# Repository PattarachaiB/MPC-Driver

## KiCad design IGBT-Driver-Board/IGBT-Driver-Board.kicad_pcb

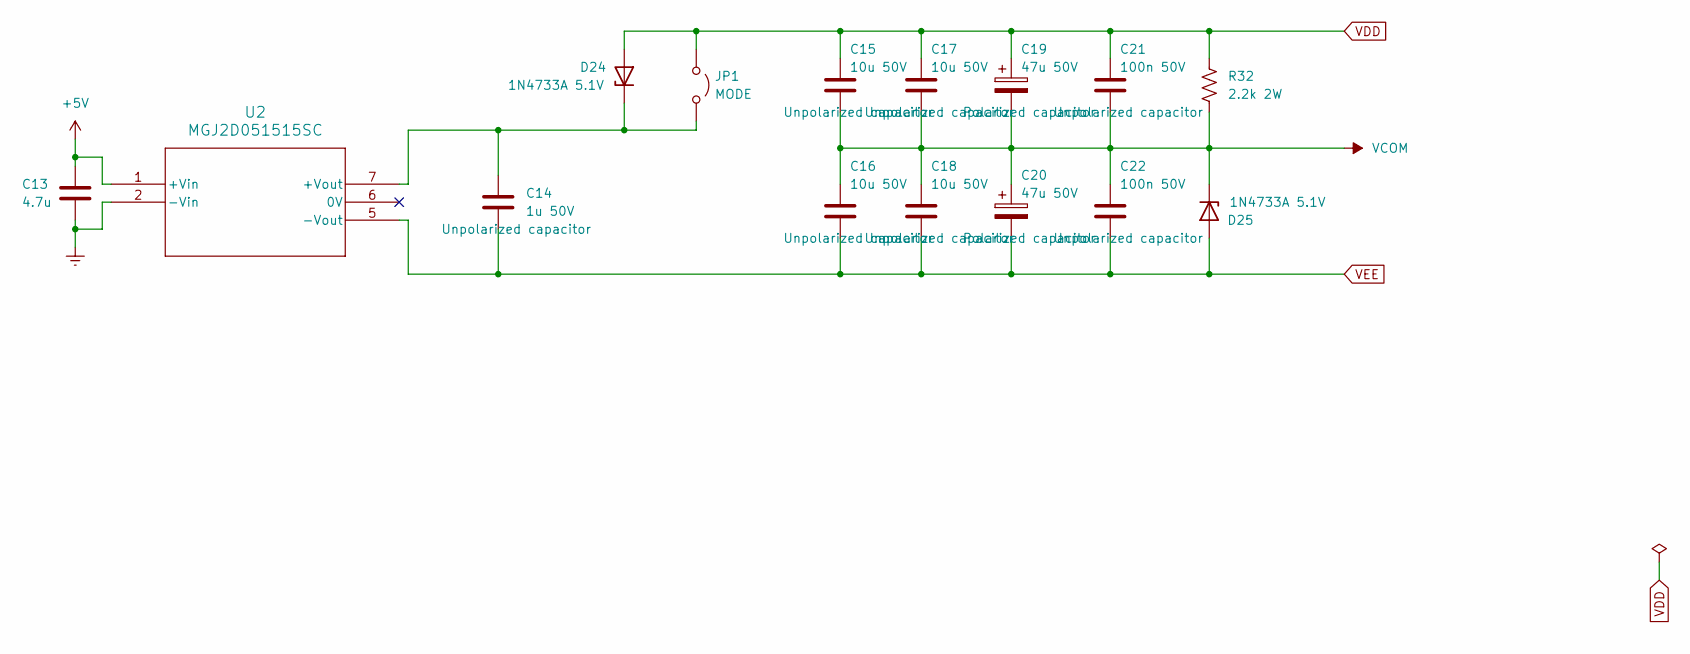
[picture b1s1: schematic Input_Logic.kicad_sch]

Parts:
C13: 4.7u; RDEC71H475K2M1H03A
C14: 1u 50V; K105M20X7RF5UH5_VIS
C15, C16, C17, C18: 10u 50V; RDEC71H106K3K1H03B
C19, C20: 47u 50V; CP_Radial_D6.3mm_P2.50mm
C21, C22: 100n 50V; RDER71H104K0M1H03A
D24, D25: 1N4733A 5.1V; D_DO-41_SOD81_P7.62mm_Horizontal
JP1: MODE; PinHeader_1x02_P2.54mm_Vertical
R32: 2.2k 2W; R_Axial_DIN0516_L15.5mm_D5.0mm_P20.32mm_Horizontal
U2: MGJ2D051515SC; MGJ2_MUR

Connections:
+5V: C13.1, U2.1 (+Vin); also elsewhere on the board
GNDREF: C13.2, U2.2 (-Vin); also elsewhere on the board
unnamed: C14.1, D24.1 (K), JP1.2 (B), U2.7 (+Vout)
VCOM: C15.2, C16.1, C17.2, C18.1, C19.2, C20.1, C21.2, C22.1, D25.1 (K), R32.1; also elsewhere on the board
VDD: C15.1, C17.1, C19.1, C21.1, D24.2 (A), JP1.1 (A), R32.2; also elsewhere on the board
VEE: C14.2, C16.2, C18.2, C20.2, C22.2, D25.2 (A), U2.5 (-Vout); also elsewhere on the board

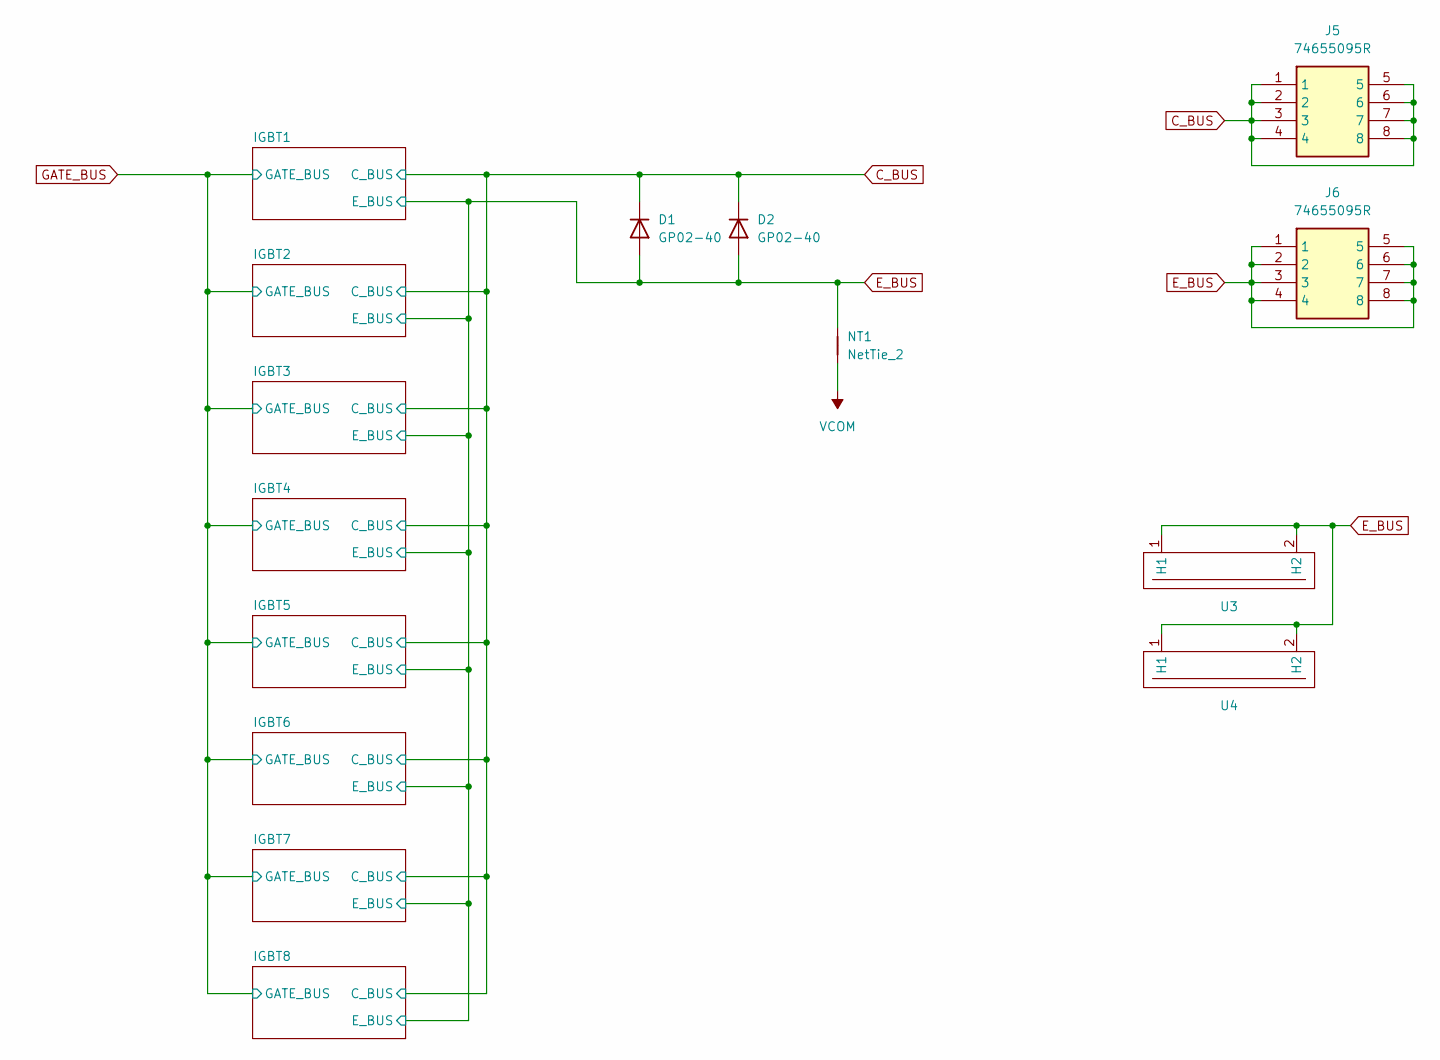
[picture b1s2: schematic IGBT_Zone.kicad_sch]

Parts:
D1, D2: GP02-40; D_DO-41_P20.32mm_HV_Horizontal
J5, J6: 74655095R; Mouser Part Number 710-74655095R
NT1: NetTie_2; NetTie-2_SMD_Pad6.0mm
U3: Heatsink_150x20x6mm
U4: Heatsink_150x20x6mm_flip

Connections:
C_BUS: D1.1 (K), D2.1 (K), J5.1, J5.2, J5.3, J5.4, J5.5, J5.6, J5.7, J5.8; also elsewhere on the board
E_BUS: D1.2 (A), D2.2 (A), J6.1, J6.2, J6.3, J6.4, J6.5, J6.6, J6.7, J6.8, NT1.2, U3.1 (H1), U3.2 (H2), U4.1 (H1), U4.2 (H2); also elsewhere on the board
VCOM: NT1.1; also elsewhere on the board

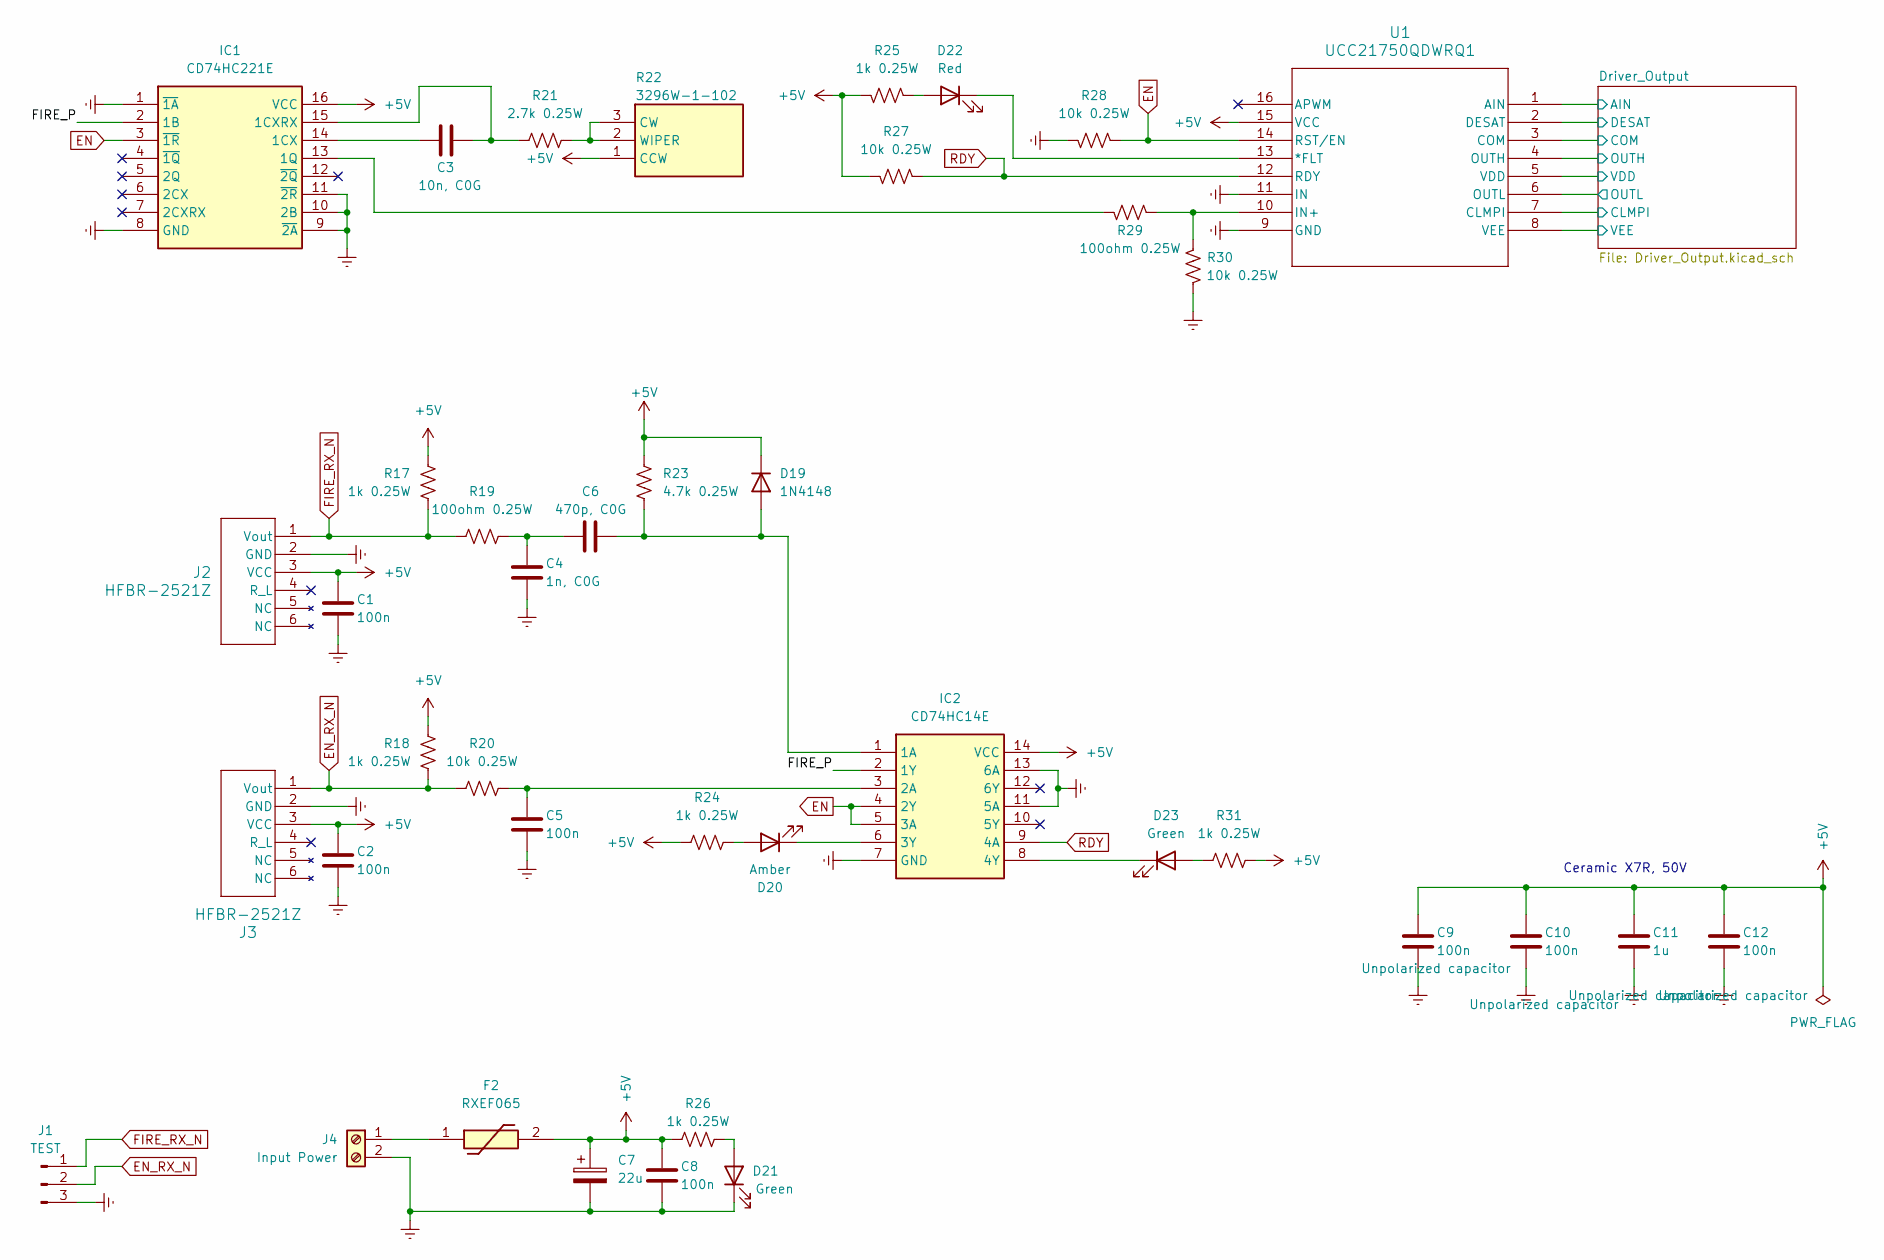
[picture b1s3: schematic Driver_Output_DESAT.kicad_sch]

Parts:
C1, C2, C5, C8, C9, C10, C12: 100n; RDER71H104K0M1H03A
C3: 10n, C0G; C330C103J5G5TA
C4: 1n, C0G; C330C103J5G5TA
C6: 470p, C0G; C330C103J5G5TA
C7: 22u; CP_Radial_D5.0mm_P2.00mm
C11: 1u; K105M20X7RF5UH5_VIS
D19: 1N4148; D_DO-35_SOD27_P7.62mm_Horizontal
D20: Amber; LED_D5.0mm_Clear
D21, D23: Green; LED_D5.0mm_Clear
D22: Red; LED_D5.0mm_Clear
F2: RXEF065; Mouser Part Number 650-RXEF065
IC1: CD74HC221E; DIP794W53P254L1930H508Q16N; Mouser Part Number 595-CD74HC221E
IC2: CD74HC14E; DIP794W53P254L1930H508Q14N; Mouser Part Number 595-CD74HC14E
J1: TEST; PinHeader_1x03_P2.54mm_Vertical
J2, J3: HFBR-2521Z
J4: Input Power; TerminalBlock_Phoenix_MKDS-1,5-2_1x02_P5.00mm_Horizontal
R17, R18, R24, R25, R26, R31: 1k 0.25W; R_Axial_DIN0207_L6.3mm_D2.5mm_P10.16mm_Horizontal
R19, R29: 100ohm 0.25W; R_Axial_DIN0207_L6.3mm_D2.5mm_P10.16mm_Horizontal
R20, R27, R28, R30: 10k 0.25W; R_Axial_DIN0207_L6.3mm_D2.5mm_P10.16mm_Horizontal
R21: 2.7k 0.25W; R_Axial_DIN0207_L6.3mm_D2.5mm_P10.16mm_Horizontal
R22: 3296W-1-102; 3296W1503LF; Mouser Part Number 652-3296W-1-104
R23: 4.7k 0.25W; R_Axial_DIN0207_L6.3mm_D2.5mm_P10.16mm_Horizontal
U1: UCC21750QDWRQ1; SOIC16_DW_TEX

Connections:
+5V: C1.1, C2.1, C7.1, C8.1, C9.1, C10.1, C11.1, C12.1, D19.1 (K), F2.2, IC1.16 (VCC), IC2.14 (VCC), J2.3 (VCC), J3.3 (VCC), R17.2, R18.2, R22.1 (CCW), R23.2, R24.1, R25.2, R26.2, R27.2, R31.2, U1.15 (VCC); also elsewhere on the board
/Driver_Output_DESAT/Driver_Output/DESAT: U1.2 (DESAT); also elsewhere on the board
/Driver_Output_DESAT/FIRE_P: IC1.2 (1B), IC2.2 (1Y)
EN: IC1.3 (~1R), IC2.4 (2Y), IC2.5 (3A), R28.1, U1.14 (RST/EN)
EN_RX_N: J1.2, J3.1 (Vout), R18.1, R20.1
FIRE_RX_N: J1.1, J2.1 (Vout), R17.1, R19.1
GATE_BUS: U1.4 (OUTH), U1.6 (OUTL), U1.7 (CLMPI); also elsewhere on the board
GNDREF: C1.2, C2.2, C4.2, C5.2, C7.2, C8.2, C9.2, C10.2, C11.2, C12.2, D21.1 (K), IC1.1 (~1A), IC1.8 (GND), IC1.9 (~2A), IC1.10 (2B), IC1.11 (~2R), IC2.7 (GND), IC2.11 (5A), IC2.13 (6A), J1.3, J2.2 (GND), J3.2 (GND), J4.2, R28.2, R30.2, U1.9 (GND), U1.11 (IN); also elsewhere on the board
unnamed: C4.1, C6.2, R19.2
unnamed: C6.1, D19.2 (A), IC2.1 (1A), R23.1
unnamed: D20.2 (A), R24.2
unnamed: D20.1 (K), IC2.6 (3Y)
unnamed: D21.2 (A), R26.1
unnamed: D22.2 (A), R25.1
unnamed: D22.1 (K), U1.13 (*FLT)
unnamed: D23.2 (A), R31.1
unnamed: D23.1 (K), IC2.8 (4Y)
unnamed: C3.1, IC1.14 (1CX)
unnamed: C3.2, IC1.15 (1CXRX), R21.2
unnamed: IC1.13 (1Q), R29.2
unnamed: C5.1, IC2.3 (2A), R20.2
unnamed: F2.1, J4.1
unnamed: R21.1, R22.2 (WIPER), R22.3 (CW)
unnamed: R29.1, R30.1, U1.10 (IN+)
RDY: IC2.9 (4A), R27.1, U1.12 (RDY)
VCOM: U1.1 (AIN), U1.3 (COM); also elsewhere on the board
VDD: U1.5 (VDD); also elsewhere on the board
VEE: U1.8 (VEE); also elsewhere on the board

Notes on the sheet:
Ceramic X7R, 50V

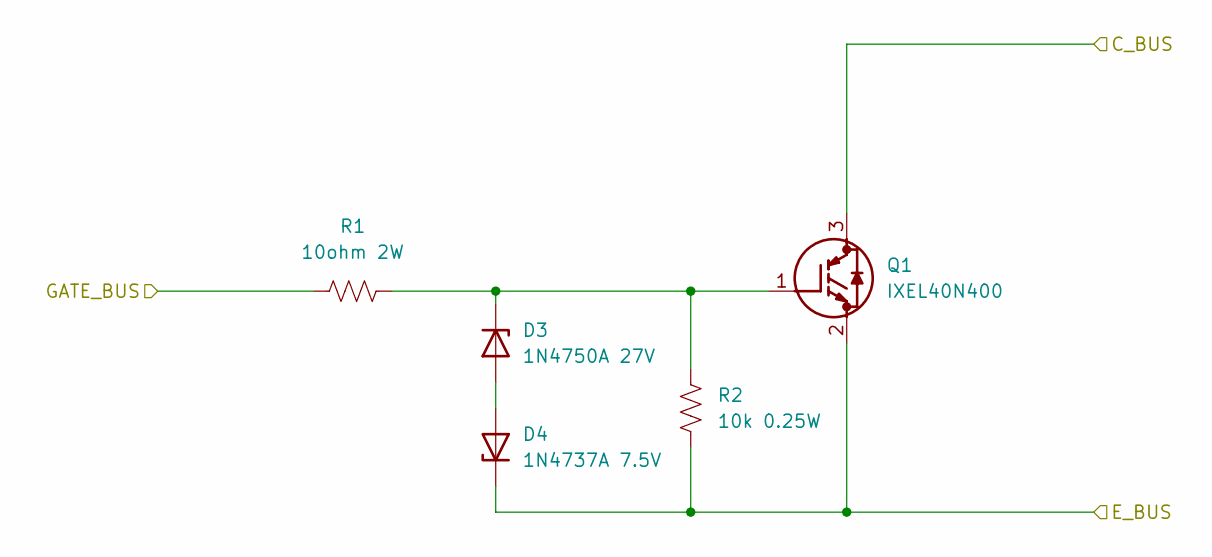
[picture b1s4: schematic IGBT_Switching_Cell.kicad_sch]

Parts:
D3: 1N4750A 27V; D_DO-41_SOD81_P7.62mm_Horizontal
D4: 1N4737A 7.5V; D_DO-41_SOD81_P7.62mm_Horizontal
Q1: IXEL40N400; IXBL60N360; Manufacturer_Part_Number IXEL40N400; Mouser Part Number 747-IXEL40N400
R1: 10ohm 2W; R_Axial_DIN0516_L15.5mm_D5.0mm_P20.32mm_Horizontal
R2: 10k 0.25W; R_Axial_DIN0207_L6.3mm_D2.5mm_P10.16mm_Horizontal

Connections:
C_BUS: Q1.3 (C); also elsewhere on the board
E_BUS: D4.1 (K), Q1.2 (E), R2.2; also elsewhere on the board
GATE_BUS: R1.1; also elsewhere on the board
unnamed: D3.2 (A), D4.2 (A)
unnamed: D3.1 (K), Q1.1 (G), R1.2, R2.1

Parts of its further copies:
D5, D7, D9, D11, D13, D15, D17: 1N4750A 27V; D_DO-41_SOD81_P7.62mm_Horizontal
D6, D8, D10, D12, D14, D16, D18: 1N4737A 7.5V; D_DO-41_SOD81_P7.62mm_Horizontal
Q2, Q3, Q4, Q5, Q6, Q7, Q8: IXEL40N400; IXBL60N360; Manufacturer_Part_Number IXEL40N400; Mouser Part Number 747-IXEL40N400
R3, R5, R7, R9, R11, R13, R15: 10ohm 2W; R_Axial_DIN0516_L15.5mm_D5.0mm_P20.32mm_Horizontal
R4, R6, R8, R10, R12, R14, R16: 10k 0.25W; R_Axial_DIN0207_L6.3mm_D2.5mm_P10.16mm_Horizontal

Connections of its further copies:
C_BUS: Q2.3 (C), Q3.3 (C), Q4.3 (C), Q5.3 (C), Q6.3 (C), Q7.3 (C), Q8.3 (C); also elsewhere on the board
E_BUS: D6.1 (K), D8.1 (K), D10.1 (K), D12.1 (K), D14.1 (K), D16.1 (K), D18.1 (K), Q2.2 (E), Q3.2 (E), Q4.2 (E), Q5.2 (E), Q6.2 (E), Q7.2 (E), Q8.2 (E), R4.2, R6.2, R8.2, R10.2, R12.2, R14.2, R16.2; also elsewhere on the board
GATE_BUS: R3.1, R5.1, R7.1, R9.1, R11.1, R13.1, R15.1; also elsewhere on the board
unnamed: D5.2 (A), D6.2 (A)
unnamed: D5.1 (K), Q2.1 (G), R3.2, R4.1
unnamed: D7.2 (A), D8.2 (A)
unnamed: D7.1 (K), Q3.1 (G), R5.2, R6.1
unnamed: D9.1 (K), Q4.1 (G), R7.2, R8.1
unnamed: D9.2 (A), D10.2 (A)
unnamed: D11.2 (A), D12.2 (A)
unnamed: D11.1 (K), Q5.1 (G), R9.2, R10.1
unnamed: D13.2 (A), D14.2 (A)
unnamed: D13.1 (K), Q6.1 (G), R11.2, R12.1
unnamed: D15.2 (A), D16.2 (A)
unnamed: D15.1 (K), Q7.1 (G), R13.2, R14.1
unnamed: D17.2 (A), D18.2 (A)
unnamed: D17.1 (K), Q8.1 (G), R15.2, R16.1

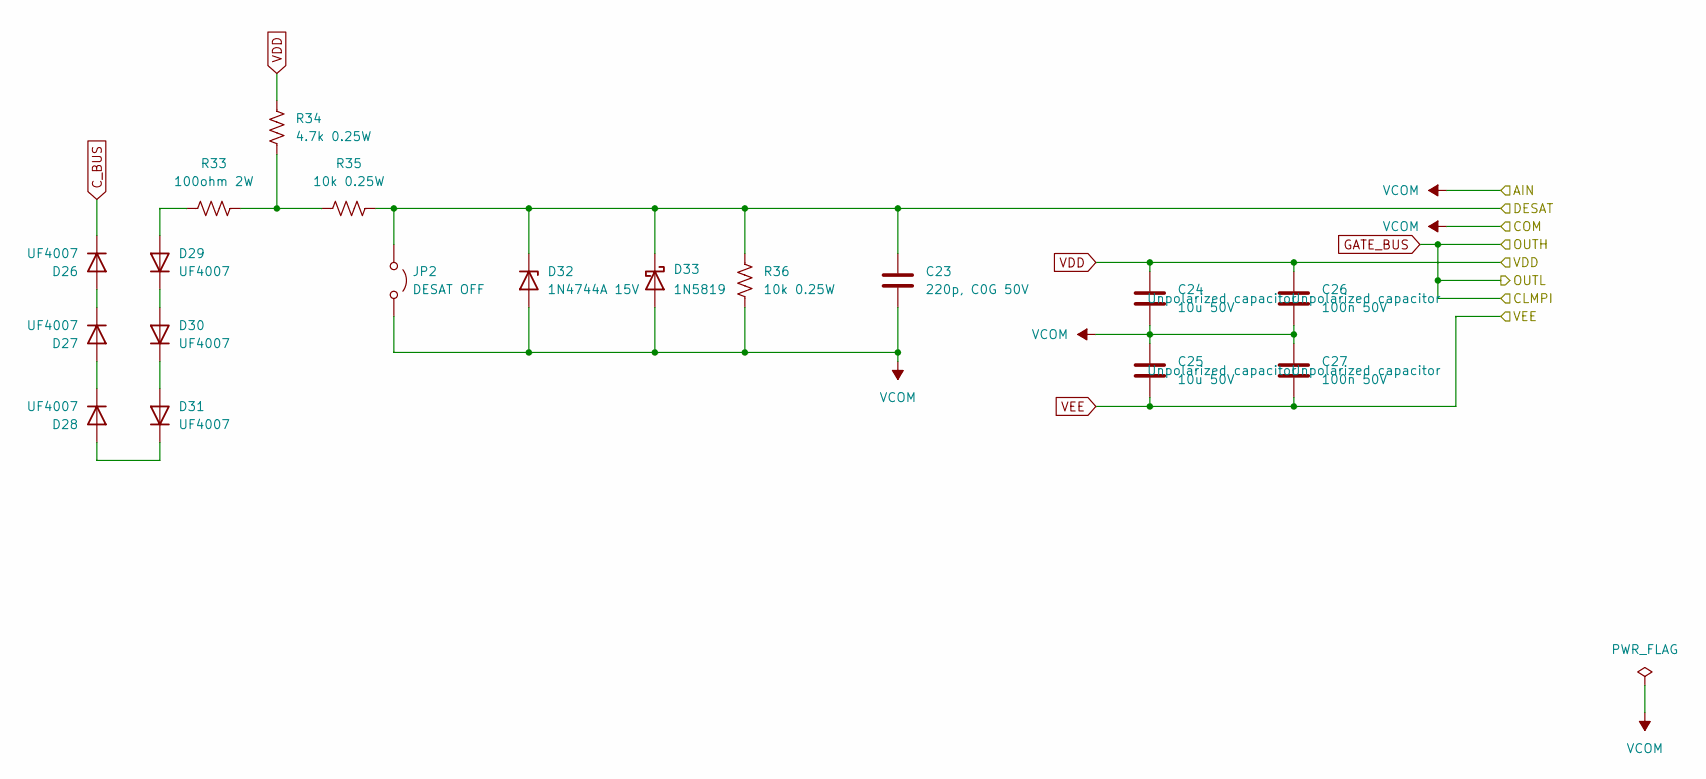
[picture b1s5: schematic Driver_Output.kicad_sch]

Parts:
C23: 220p, C0G 50V; C330C103J5G5TA
C24, C25: 10u 50V; RDEC71H106K3K1H03B
C26, C27: 100n 50V; RDER71H104K0M1H03A
D26, D27, D28, D29, D30, D31: UF4007; D_DO-41_SOD81_P10.16mm_Horizontal
D32: 1N4744A 15V; D_DO-41_SOD81_P7.62mm_Horizontal
D33: 1N5819; D_DO-41_SOD81_P10.16mm_Horizontal
JP2: DESAT OFF; PinHeader_1x02_P2.54mm_Vertical
R33: 100ohm 2W; R_Axial_DIN0516_L15.5mm_D5.0mm_P20.32mm_Horizontal
R34: 4.7k 0.25W; R_Axial_DIN0207_L6.3mm_D2.5mm_P10.16mm_Horizontal
R35, R36: 10k 0.25W; R_Axial_DIN0207_L6.3mm_D2.5mm_P10.16mm_Horizontal

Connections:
/Driver_Output_DESAT/Driver_Output/DESAT: C23.1, D32.1 (K), D33.1 (K), JP2.1 (A), R35.2, R36.1; also elsewhere on the board
C_BUS: D26.1 (K); also elsewhere on the board
unnamed: D26.2 (A), D27.1 (K)
unnamed: D27.2 (A), D28.1 (K)
unnamed: D28.2 (A), D31.1 (K)
unnamed: D29.2 (A), R33.1
unnamed: D29.1 (K), D30.2 (A)
unnamed: D30.1 (K), D31.2 (A)
unnamed: R33.2, R34.1, R35.1
VCOM: C23.2, C24.2, C25.1, C26.2, C27.1, D32.2 (A), D33.2 (A), JP2.2 (B), R36.2; also elsewhere on the board
VDD: C24.1, C26.1, R34.2; also elsewhere on the board
VEE: C25.2, C27.2; also elsewhere on the board

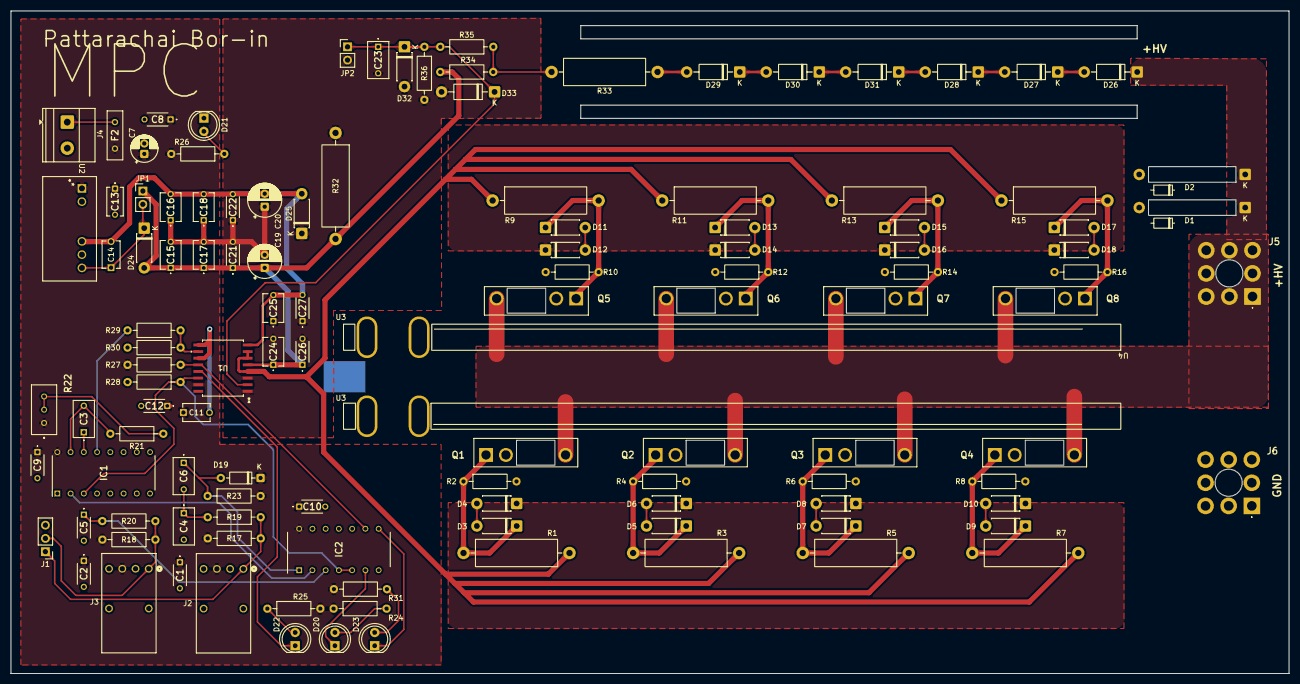
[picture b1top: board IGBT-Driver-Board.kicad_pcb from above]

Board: 2 copper layers, 245.0 x 127.0 mm, 120 parts (1 on the bottom side), 54 nets.
